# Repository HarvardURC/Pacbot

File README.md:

# PacBot
Repository for the Harvard Undergraduate Robotics Club's PacBot team

> NOTE: Because this repository includes submodules, it should be cloned using `git clone --recursive`.

The rules for PacBot and helpful images can be found at our website: https://harvardrobotics.com/pacbots

Codebase for 2021-2022 can be found in the ***master*** branch. Codebases for past years can be found in their respective branches.

The current Pacman game code can be found in 'src/gameEngine'. The README there describes how to run the game.

The code for the Harvard robotics team's bot can be found in the 'src/botCode' folder (if you're looking for inspiration).

Documentation for participating teams regarding the game board/arena, bot designs from past years, and how to communicate with the game can be found in the 'docs' directory. Baseline code is provided here that teams can use to code their bots.

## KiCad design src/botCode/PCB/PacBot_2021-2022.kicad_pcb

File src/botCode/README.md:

# PacBot 2021-22 Bot Code

This directory contains all of the code for the Harvard team's PacBot. Participating teams can refer to this code when designing their own bots if they'd like.

## How it works

The botcode will connect to the gameEngine Server in order to receive messages, but it will also run its own separate robomodules server for internal use. `server.py` is the internal server, `pacbotCommsModule.py` is a module that connects to both the gameEngine server and the local server, listens to the gameEngine's LightState messages and forwards them to the local server. 

## High Level Strategy Code

The high level strategy for the robot is in 'heuristicHighLevelModule.py'. This receives the game state from the local server regarding the robot's location and the location of the ghosts. It makes a decision regarding where to move the bot. It sends a PACMAN_COMMAND message to tell the bot which direction to go.

Run './heuristicHighLevelModule.py' to run the high level module.

## Low Level Code

The module 'directionLowLevelModule.py' is our current low level code module. It receives direction commands from the high level module and makes decisions on how to move the motors.

Motor movement is managed through PID loops dependent on the IR sensors. See 'low_level' directory for related code.

## Requirements

- See the 'src/environment.yml' for a conda environment with the necessary Python3 requirements.
- In order to run the bot code, you need to already have a gameEngine server running.

## How to run the code

1. Start the game engine - follow instructions in src/gameEngine.
2. Start the local bot server. 
  - Supply the correct server address:port combination in `server.py` either through environment variables or by changing the default values in the code itself. Like the game engine server, the bot server should bind to your computer's local IP address.
  - run `./server.py`.
3. Start the communications module by running `./pacbotCommsModule.py`.
  - Make sure the SERVER_ADDRESS:SERVER_PORT is the address of the game engine server and that you are on the same WiFi network as the game engine server. Make sure the LOCAL_ADDRESS:LOCAL_PORT is the adress of the local bot server (and that you're on the same WiFi network as the local server).
4. Start all other desired modules (i.e. heuristicHighLevelModule and directionLowLevelModule).

## Other Modules

pacbotSimulatorModule.py

Running this module will allow you to simulate the heuristicHighLevelModule playing the game. It communicates the moves the high level module makes to the game engine.

keyboardModule.py

This module should allow you to control the PacBot with your keyboard AWSD keys.

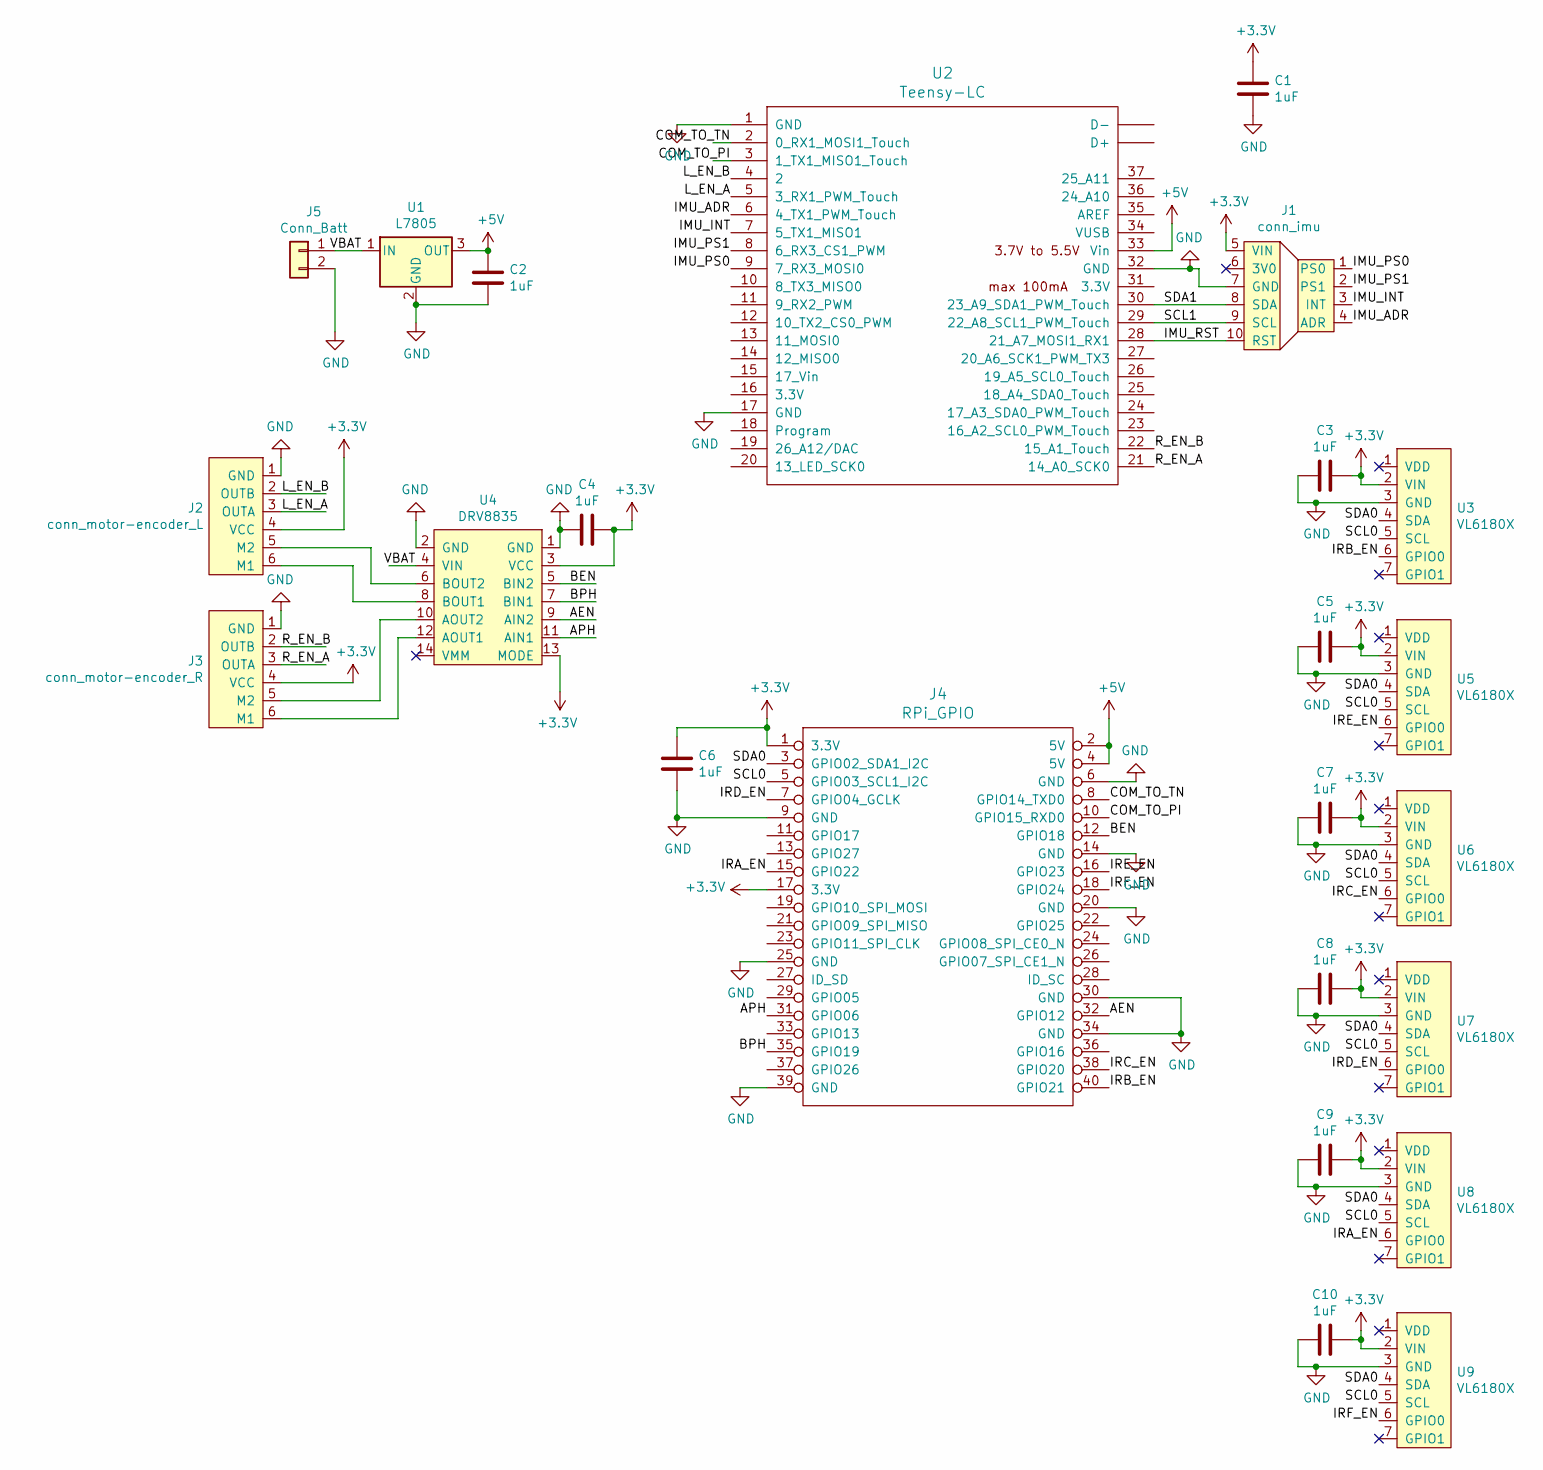
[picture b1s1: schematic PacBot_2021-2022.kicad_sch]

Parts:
C1, C2, C3, C4, C5, C6, C7, C8, C9, C10: 1uF; C_0603_1608Metric
J1: conn_imu
J2: conn_motor-encoder_L; JST_PH_B6B-PH-K_1x06_P2.00mm_Vertical
J3: conn_motor-encoder_R; JST_PH_B6B-PH-K_1x06_P2.00mm_Vertical
J4: RPi_GPIO; ADA3708_RPI-ZERO
J5: Conn_Batt; JST_PH_B2B-PH-K_1x02_P2.00mm_Vertical
U1: L7805; Stocko_MKS_1653-6-0-303_1x3_P2.50mm_Vertical
U2: Teensy-LC; Teensy30_31_32_LC
U3, U5, U6, U7, U8, U9: VL6180X; conn_ir
U4: DRV8835; drv8835

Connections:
+3V3: C1.1, C3.2, C4.1, C5.1, C6.1, C7.1, C8.1, C9.1, C10.1, J1.5 (VIN), J2.4 (VCC), J3.4 (VCC), J4.1 (3.3V), J4.17 (3.3V), U3.2 (VIN), U4.3 (VCC), U4.13 (MODE), U5.2 (VIN), U6.2 (VIN), U7.2 (VIN), U8.2 (VIN), U9.2 (VIN)
+5V: C2.1, J4.2 (5V), J4.4 (5V), U1.3 (OUT), U2.33 (Vin)
/AEN: J4.32 (GPIO12), U4.9 (AIN2)
/APH: J4.31 (GPIO06), U4.11 (AIN1)
/BEN: J4.12 (GPIO18), U4.5 (BIN2)
/BPH: J4.35 (GPIO19), U4.7 (BIN1)
/COM_TO_PI: J4.10 (GPIO15_RXD0), U2.3 (1_TX1_MISO1_Touch)
/COM_TO_TN: J4.8 (GPIO14_TXD0), U2.2 (0_RX1_MOSI1_Touch)
/IMU_ADR: J1.4 (ADR), U2.6 (4_TX1_PWM_Touch)
/IMU_INT: J1.3 (INT), U2.7 (5_TX1_MISO1)
/IMU_PS0: J1.1 (PS0), U2.9 (7_RX3_MOSI0)
/IMU_PS1: J1.2 (PS1), U2.8 (6_RX3_CS1_PWM)
/IMU_RST: J1.10 (RST), U2.28 (21_A7_MOSI1_RX1)
/IRA_EN: J4.15 (GPIO22), U8.6 (GPIO0)
/IRB_EN: J4.40 (GPIO21), U3.6 (GPIO0)
/IRC_EN: J4.38 (GPIO20), U6.6 (GPIO0)
/IRD_EN: J4.7 (GPIO04_GCLK), U7.6 (GPIO0)
/IRE_EN: J4.16 (GPIO23), U5.6 (GPIO0)
/IRF_EN: J4.18 (GPIO24), U9.6 (GPIO0)
/L_EN_A: J2.3 (OUTA), U2.5 (3_RX1_PWM_Touch)
/L_EN_B: J2.2 (OUTB), U2.4 (2)
/R_EN_A: J3.3 (OUTA), U2.21 (14_A0_SCK0)
/R_EN_B: J3.2 (OUTB), U2.22 (15_A1_Touch)
/SCL0: J4.5 (GPIO03_SCL1_I2C), U3.5 (SCL), U5.5 (SCL), U6.5 (SCL), U7.5 (SCL), U8.5 (SCL), U9.5 (SCL)
/SCL1: J1.9 (SCL), U2.29 (22_A8_SCL1_PWM_Touch)
/SDA0: J4.3 (GPIO02_SDA1_I2C), U3.4 (SDA), U5.4 (SDA), U6.4 (SDA), U7.4 (SDA), U8.4 (SDA), U9.4 (SDA)
/SDA1: J1.8 (SDA), U2.30 (23_A9_SDA1_PWM_Touch)
/VBAT: J5.1, U1.1 (IN), U4.4 (VIN)
GND: C1.2, C2.2, C3.1, C4.2, C5.2, C6.2, C7.2, C8.2, C9.2, C10.2, J1.7 (GND), J2.1 (GND), J3.1 (GND), J4.6 (GND), J4.9 (GND), J4.14 (GND), J4.20 (GND), J4.25 (GND), J4.30 (GND), J4.34 (GND), J4.39 (GND), J5.2, U1.2 (GND), U2.1 (GND), U2.17 (GND), U2.32 (GND), U3.3 (GND), U4.1 (GND), U4.2 (GND), U5.3 (GND), U6.3 (GND), U7.3 (GND), U8.3 (GND), U9.3 (GND)
unnamed: J2.5 (M2), U4.6 (BOUT2)
unnamed: J2.6 (M1), U4.8 (BOUT1)
unnamed: J3.5 (M2), U4.10 (AOUT2)
unnamed: J3.6 (M1), U4.12 (AOUT1)

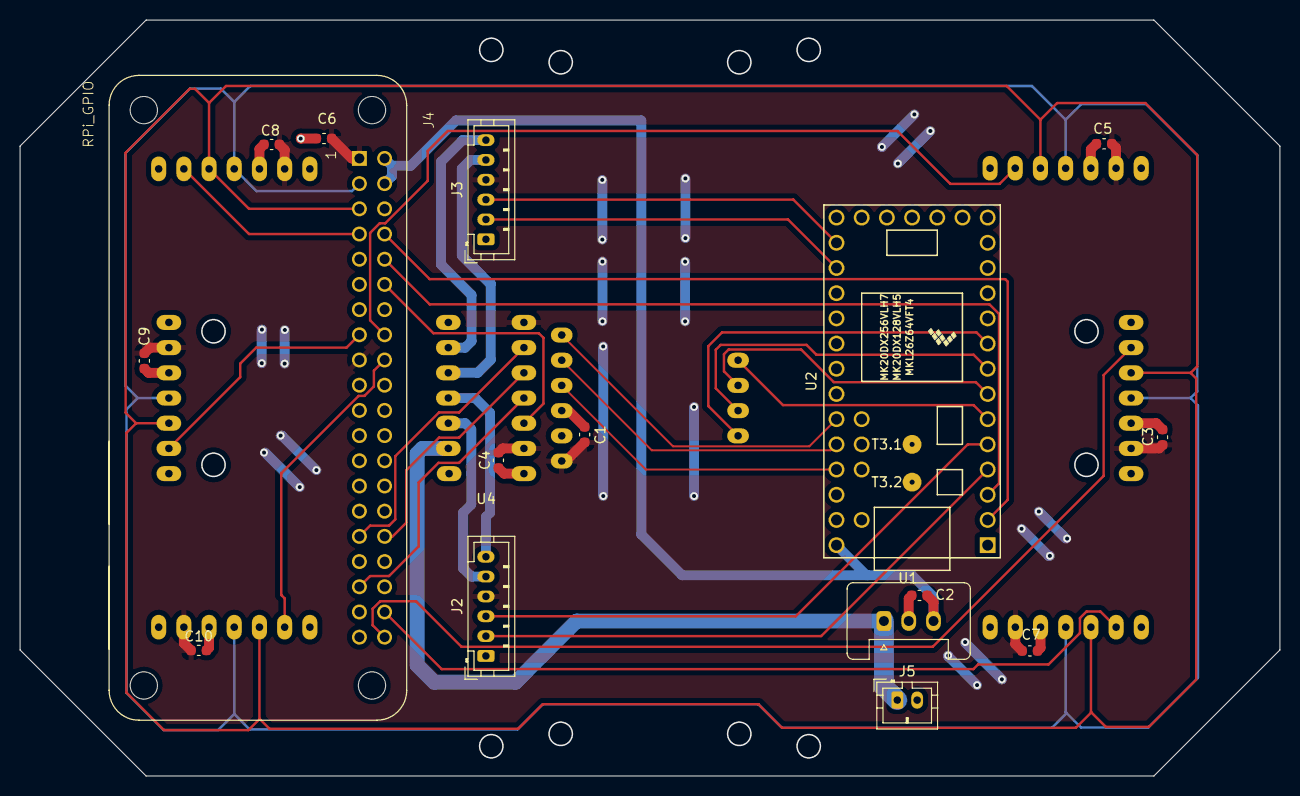
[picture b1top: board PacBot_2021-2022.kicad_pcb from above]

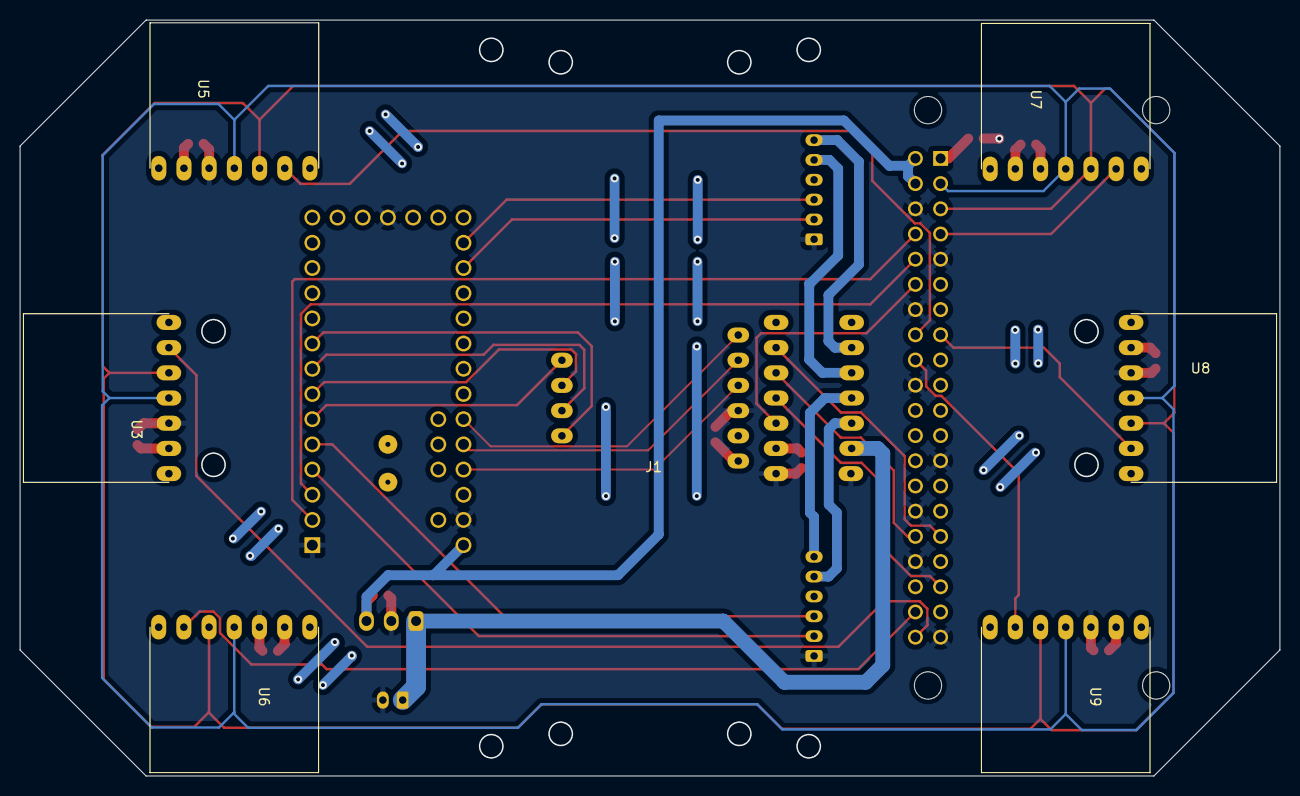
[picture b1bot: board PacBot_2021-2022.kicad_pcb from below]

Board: 2 copper layers, 127.0 x 76.2 mm, 24 parts (7 on the bottom side), 33 nets.

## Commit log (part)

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2017-12-02 errors fixed
2017-12-02 encoders changed
2017-12-03 grid and legends added
2017-12-03 Capitalization fixed
2018-01-11 Add to gameEngine README instructions.
2018-01-11 Add to gameEngine README instructions. (#24)
2018-01-27 grids for path types renames. Working on controllers all motors for bot movement. Testing will start as soon as the bot is assembled
2018-01-28 fix camera reader vol1
2018-02-17 latest changes
2018-02-24 none
2018-03-03 latest commit from pi
2018-03-03 encoderTest edited
2018-03-03 encoders
2018-03-03 encoders changes
2018-03-24 PID changed
2018-03-24 test
2018-03-31 motors
2018-03-31 motors2
2018-03-31 motorTest changes
2018-04-07 wall follow
2018-04-07 wall follow edited
2018-04-14 Vision Code
2018-04-14 Transform code!
2018-04-14 motors.py changed
2018-04-14 motors edited
2018-04-14 add dots
2018-04-21 bot tracking works
2018-04-21 motors updated
2018-04-21 motors syntax fixed
2018-04-21 motors.py
2018-04-21 motor logic restructure hand off
2018-04-21 motors2 updated
2018-04-21 straight inserted
2018-04-21 tracking works
2018-04-21 single sensor modes added
2018-04-21 add keyboard simulator
2018-04-21 extra condition addition hand off
2018-04-21 new condition added for tie breaking
2018-04-21 P value updated
2018-04-21 cleanup
2018-04-21 camels
2018-04-21 turning code
2018-04-22 conditions
2018-04-22 clean up
2018-04-22 yeeehaw
2018-04-23 test.py
2018-04-23 new encoder code
2018-04-23 old encoders
2018-04-23 current
2018-04-23 latest
2018-04-23 c encoders
2018-04-23 encoder test
2018-04-23 python c interface
2018-04-24 pigpio
2018-04-24 go back to last commit
2018-04-24 library
2018-04-24 encoder callback
2018-04-24 encoder callback needs to be in function
2018-04-24 make setup executable
2018-04-24 rmeove print
2018-04-24 argsss
2018-04-24 change encoder libraries
2018-04-25 push
2018-04-26 no camera low level
2018-04-26 new motor tunings
2018-04-26 reverse direction
2018-04-26 vision works
2018-04-26 added fail safe
2018-04-26 diagonal sensors
2018-04-26 make vision image smaller
2018-04-26 latest, without diagonal sensors
2018-04-26 Low level (#26)
    * added the initial codes for super low level control
    * cleanup
    * work on lowLevelModule
    * GPIO helpers updated to add millis function. PID library added
    * motor.py modified to supoort speed sepcification. motorTest modified correspondingly. PID.py modified to add output() module. WallFollowTest added. The scope of variables need to determined while t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
    * fixed indentation in wallFollowTest
2018-04-26 latest changes from pi
2018-04-28 latest code from pi
2018-04-28 change to heuristics
2018-04-28 latest from pi
2019-04-06 working things
2019-06-29 Add working arena 2018-2019
2019-10-12 Overview changes
2019-10-20 Added 2019-2020
2019-10-29 Updated Docs
2020-01-27 Added PCB Files
2020-02-23 Added blinking to vulnerable ghosts and cherry spawning
2020-10-24 copying 2019-2020 into 2020-2021
2020-10-27 added robomodules submodule
2020-10-27 changing submodule stuff
2020-10-28 updating gitignore for c++
2020-10-28 adding deque and pid stuff
2020-10-28 more progress on pid and deque
2020-10-28 seems like a working pid class to me. Untested though
2020-10-28 copying in rotaryEncoder
2020-10-28 adding readmes
2020-10-28 adding motor and tof templates, no functionality yet
2020-10-28 adding imu file
2020-10-29 robot state implemented, robotstatehistory.hpp almost finished
2020-10-31 more stuff
2020-11-01 rsh done, untested still
2020-11-01 deque stuff
2020-11-01 twas in the wrong branch
2020-11-01 addded globalState
2020-11-02 calling globalstate from master
2020-11-07 adding botcode stuff
2021-02-01 added Makefile. Still not working; deque is fucked, probably other stuff too
2021-02-01 try running this to see the error: g++ -std=c++14 -c -Wall utils/conversions.cpp dataTypes/deque.cpp controllers/pid.cpp
2021-02-10 initial bfs work in c++
2021-02-13 it compiles :)
2021-02-13 Bump httplib2 from 0.9.2 to 0.19.0
    Bumps [httplib2](https://github.com/httplib2/httplib2) from 0.9.2 to 0.19.0.
    - [Release notes](https://github.com/httplib2/httplib2/releases)
    - [Changelog](https://github.com/httplib2/httplib2/blob/master/CHANGELOG)
    - [Commits](https://github.com/httplib2/httplib2/compare/0.9.2...v0.19.0)
2021-02-13 Bump psutil from 5.5.1 to 5.6.6
    Bumps [psutil](https://github.com/giampaolo/psutil) from 5.5.1 to 5.6.6.
    - [Release notes](https://github.com/giampaolo/psutil/releases)
    - [Changelog](https://github.com/giampaolo/psutil/blob/master/HISTORY.rst)
    - [Commits](https://github.com/giampaolo/psutil/compare/release-5.5.1...release-5.6.6)
2021-02-13 Bump pillow from 5.4.1 to 7.1.0
    Bumps [pillow](https://github.com/python-pillow/Pillow) from 5.4.1 to 7.1.0.
    - [Release notes](https://github.com/python-pillow/Pillow/releases)
    - [Changelog](https://github.com/python-pillow/Pillow/blob/master/CHANGES.rst)
    - [Commits](https://github.com/python-pillow/Pillow/compare/5.4.1...7.1.0)
2021-02-13 fixing some imports
2021-02-13 updating loop()
2021-02-13 updating stuff
2021-02-14 moving back to custom home-made deque
2021-02-20 sensors/actuators
2021-02-20 sensors/actuators2
2021-02-20 sensors/actuators3
2021-02-20 sensor readmes added
2021-02-20 comments about k_predict
2021-02-20 comment reformatted
2021-02-23 clean up files/edit READMEs
2021-02-23 theoretically a wall follower
2021-02-23 makefile
2021-02-23 commented out est/updater includes
2021-02-23 fixing wall follower
2021-02-23 tof names
2021-02-23 changing to .h
2021-02-23 changing sensors/motor
2021-02-23 more changes
2021-02-23 makefile update
2021-02-23 im dumb
2021-02-23 adding prints
2021-02-23 stdio
2021-03-19 Bump pillow from 5.4.1 to 8.1.1
    Bumps [pillow](https://github.com/python-pillow/Pillow) from 5.4.1 to 8.1.1.
    - [Release notes](https://github.com/python-pillow/Pillow/releases)
    - [Changelog](https://github.com/python-pillow/Pillow/blob/master/CHANGES.rst)
    - [Commits](https://github.com/python-pillow/Pillow/compare/5.4.1...8.1.1)
2021-03-20 updated makefile and global sensors/actuators
2021-03-26 Bump pyyaml from 3.13 to 5.4
    Bumps [pyyaml](https://github.com/yaml/pyyaml) from 3.13 to 5.4.
    - [Release notes](https://github.com/yaml/pyyaml/releases)
    - [Changelog](https://github.com/yaml/pyyaml/blob/master/CHANGES)
    - [Commits](https://github.com/yaml/pyyaml/compare/3.13...5.4)
2021-04-10 fixed deque
2021-04-17 new branch
2021-05-16 some edits
2021-05-21 aww man we looking better
2021-05-22 testing
2021-05-22 fixed dque, and now pid is passing too thank god
2021-05-23 did someone say testssss
2021-05-25 oh, did someone say that the particle filter is working? Damnnnn
2021-05-25 some updated to particle filter, so it works more nicely with stuff that uses extra stuff in the past
2021-05-26 more edits
2021-05-26 oops lolll
2021-06-08 Bump pillow from 5.4.1 to 8.2.0
    Bumps [pillow](https://github.com/python-pillow/Pillow) from 5.4.1 to 8.2.0.
    - [Release notes](https://github.com/python-pillow/Pillow/releases)
    - [Changelog](https://github.com/python-pillow/Pillow/blob/master/CHANGES.rst)
    - [Commits](https://github.com/python-pillow/Pillow/compare/5.4.1...8.2.0)
    ---
    updated-dependencies:
2021-09-08 Bump pillow from 5.4.1 to 8.3.2
    Bumps [pillow](https://github.com/python-pillow/Pillow) from 5.4.1 to 8.3.2.
    - [Release notes](https://github.com/python-pillow/Pillow/releases)
    - [Changelog](https://github.com/python-pillow/Pillow/blob/master/CHANGES.rst)
    - [Commits](https://github.com/python-pillow/Pillow/compare/5.4.1...8.3.2)
    ---
    updated-dependencies:
2021-10-24 frightened ghosts reset on respawn
2021-10-27 created 2020-2021 branch
2021-10-27 deletions
2021-10-27 2017-2018 branch created
2021-10-27 2018-2019 branch created
2021-10-27 2019-2020 created
2021-10-27 restructured code base for 2021-2022
2021-10-28 some readme updates
2021-10-28 added submodule
2021-10-31 new orange respawn path, game ends even if gghosts are frightened
2021-11-14 variables.py comments, changed terminal print outs, made visualized game fit on screen
2021-11-14 resizing through command line argument
2021-11-17 added environment.yml
2021-11-17 edited the readme
2021-11-17 moved environment
2021-11-18 new env
2021-11-21 commented ghostAgent.py
2021-11-21 added various additional comments
2021-11-24 shuffling documentation
2021-11-24 updating docs
2021-12-05 more documentation
2022-01-02 remove folders
2022-01-02 clean up more
2022-01-02 added reqs.txt
2022-01-03 some docs updates
2022-01-04 update ghost paths
2022-01-04 update ghost movement
2022-01-04 reshaping through command line
2022-01-04 game bugs fixed
2022-01-04 fruit not rn
2022-01-06 working on fruit, updating messages
2022-01-07 updated grid location
2022-01-07 updated arena documentation
2022-01-16 remove robomodules submodule
2022-01-16 submodule added back
2022-01-21 updated readme for game engine
2022-01-26 bot PCB added
2022-01-26 pcb start
2022-01-26 commited a few more files
2022-01-26 removed PCB dir
2022-01-30 added board outline
2022-02-06 added the vias and guiding labels
2022-02-06 init branch
2022-02-09 shuffle public design docs
2022-02-09 Revert "shuffle public design docs"
    This reverts commit 1f18fdc1b2d93b0dda7e0a9332dcd78fc0c3774f.
2022-02-09 shuffle docs
2022-02-09 2020-21 Bot added
2022-02-09 2020-21 README added
2022-02-09 docs added for 2020-21 bot
2022-02-09 chance jpg
2022-02-09 change
2022-02-09 remove messages
2022-02-09 update to botCode
2022-02-13 FIxed cherry
2022-02-14 kinda working
2022-02-14 small changes by Tom
2022-02-20 gitignore, no DS Store
2022-02-20 ghosts reverse when changing state between chase + scatter
2022-02-20 reverses direction on frighten
2022-02-20 Added Teensy, holes need to be moved
2022-02-24 Holes moved, some more components added
2022-02-25 fixed rawdata for new I2C bus
2022-02-27 updated teensy code
2022-02-27 PCB updated
2022-02-27 fixed cherry repeat bug
2022-02-27 started on launch script
2022-02-27 removed unused import. gameEngine runs again
2022-02-27 launch.sh now closes the tabs it creates
2022-02-27 PCB components placed
2022-03-02 finished sensors script
2022-03-06 updated pcb
2022-03-06 back up included
2022-03-06 working on PCB
2022-03-09 update kicad
2022-03-11 finished pcb
2022-03-12 schematic updated
2022-03-12 visualize address updated
2022-03-27 kicad updated
2022-03-27 something?
2022-03-28 Tom changes
2022-03-28 gameState.py updated for ghost reversal
2022-03-28 ghostAgent.py updated for ghost reversal
2022-03-30 change serial
2022-03-30 read too
2022-03-31 Sensors class created for teensy
2022-03-31 sensors updated
2022-03-31 reset encoders
2022-03-31 to do updated
2022-04-05 stuff
2022-04-05 teensy code
2022-04-05 pins updated
2022-04-05 updated rpi code
2022-04-06 update sensors
2022-04-06 getting to work
2022-04-06 local updates
2022-04-08 updated code
2022-04-08 editing motors
2022-04-13 updates to low level
2022-04-13 motor test update
2022-04-13 updated motors
2022-04-13 updated sensors
2022-04-13 sensors
2022-04-13 Detects walls
2022-04-14 small updates
2022-04-14 Tweaks to turning functions to help correct via IR sensors
2022-04-16 most recent on bot
2022-04-16 init
2022-04-16 include init
2022-04-17 updates from bot
2022-04-20 possible motors update
2022-04-20 separating low and upper parts of game board
2022-04-20 no todo
2022-04-20 visualier updated
2022-04-20 ticks
2022-04-22 finishing arena
2022-08-06 added low level README
2022-08-06 remove swap file
2022-09-23 Bump protobuf from 3.19.1 to 3.19.5 in /src
    Bumps [protobuf](https://github.com/protocolbuffers/protobuf) from 3.19.1 to 3.19.5.
    - [Release notes](https://github.com/protocolbuffers/protobuf/releases)
    - [Changelog](https://github.com/protocolbuffers/protobuf/blob/main/generate_changelog.py)
    - [Commits](https://github.com/protocolbuffers/protobuf/compare/v3.19.1...v3.19.5)
    ---
    updated-dependencies:
2025-06-17 Bump protobuf from 3.19.1 to 4.25.8 in /src
    Bumps [protobuf](https://github.com/protocolbuffers/protobuf) from 3.19.1 to 4.25.8.
    - [Release notes](https://github.com/protocolbuffers/protobuf/releases)
    - [Changelog](https://github.com/protocolbuffers/protobuf/blob/main/protobuf_release.bzl)
    - [Commits](https://github.com/protocolbuffers/protobuf/compare/v3.19.1...v4.25.8)
    ---
    updated-dependencies:
